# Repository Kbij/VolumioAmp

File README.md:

# VolumioAmp
A Raspberry Pi CM4 Volumio Amplifier combination

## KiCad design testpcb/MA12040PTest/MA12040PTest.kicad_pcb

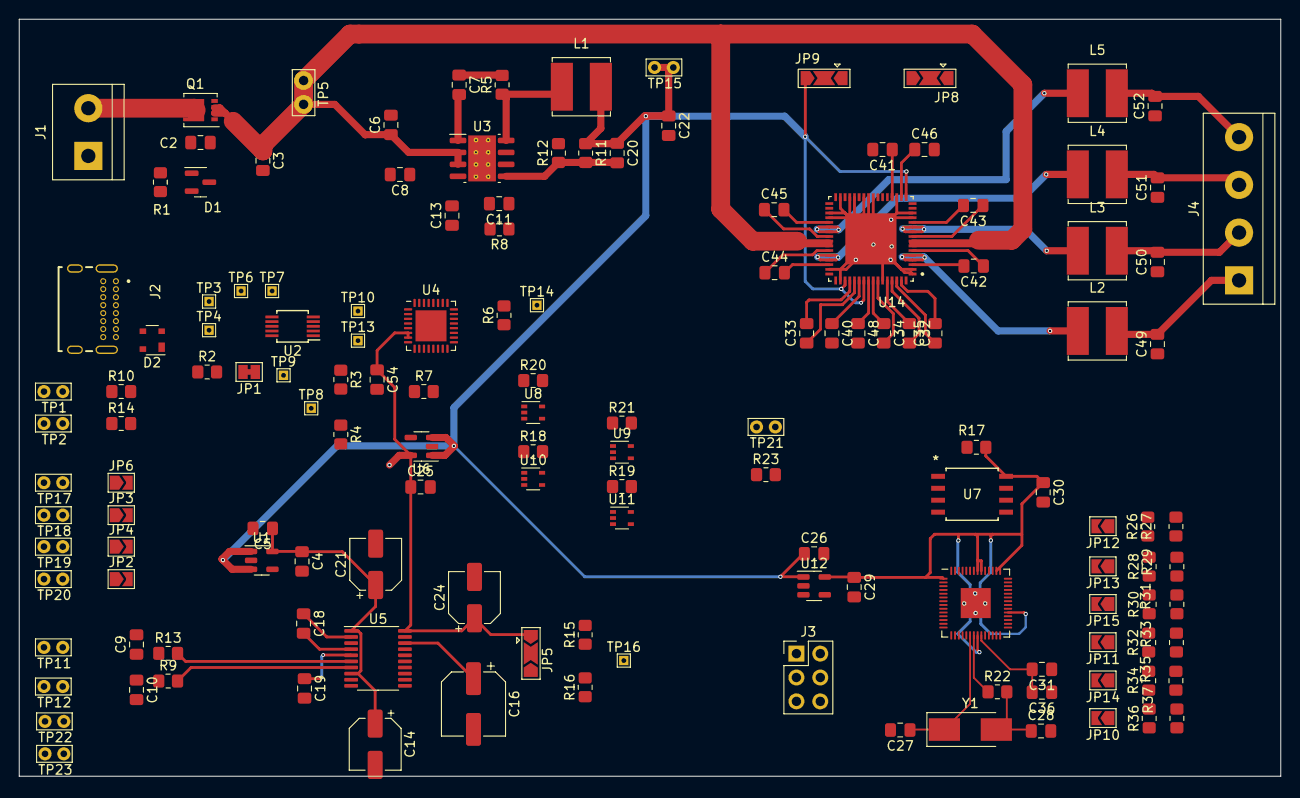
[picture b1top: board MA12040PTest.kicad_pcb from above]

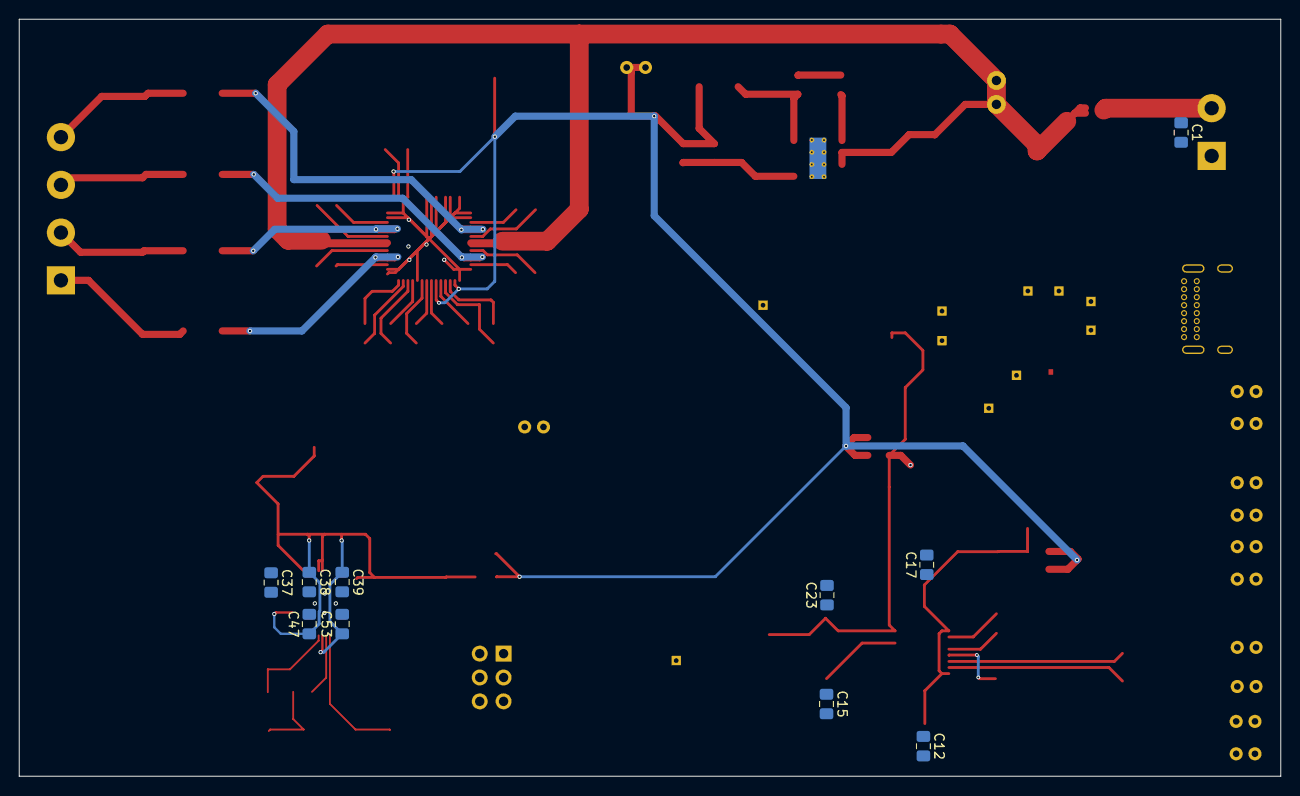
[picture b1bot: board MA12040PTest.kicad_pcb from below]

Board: 2 copper layers, 134.3 x 80.6 mm, 153 parts (10 on the bottom side), 100 nets.

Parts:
C1, C2, C7, C8, C12, C15, C17, C23, C30, C31, C35, C37, C38, C39, C47, C53: 100n; C_0805_2012Metric_Pad1.18x1.45mm_HandSolder
C3, C6: 10u 35v; C_0805_2012Metric_Pad1.18x1.45mm_HandSolder
C4: 10n; C_0805_2012Metric_Pad1.18x1.45mm_HandSolder
C5, C25, C26, C29, C32, C33, C34, C36, C40, C41, C46, C48, C49, C50, C51, C52, C54: 1u; C_0805_2012Metric_Pad1.18x1.45mm_HandSolder
C9, C10: 2n2; C_0805_2012Metric_Pad1.18x1.45mm_HandSolder
C11, C20: 220p; C_0805_2012Metric_Pad1.18x1.45mm_HandSolder
C13: 1.2nF; C_0805_2012Metric_Pad1.18x1.45mm_HandSolder
C14, C21, C24: 10u; CP_Elec_5x5.8
C16: 10u; CP_Elec_6.3x3.9
C18, C19: 2u2; C_0805_2012Metric_Pad1.18x1.45mm_HandSolder
C22, C42, C43, C44, C45: 10u; C_0805_2012Metric_Pad1.18x1.45mm_HandSolder
C27, C28: 22p; C_0805_2012Metric_Pad1.18x1.45mm_HandSolder
D1: MMBZ5242BLT3G; SOT-23
D2: SP0503BAHT; SOT-143
J1: 24v Input; TerminalBlock_bornier-2_P5.08mm
J2: USB4085-GF-A_REVB; GCT_USB4085-GF-A_REVB
J3: Conn_02x03_Top_Bottom; PinHeader_2x03_P2.54mm_Vertical
J4: Screw_Terminal_01x04; TerminalBlock_bornier-4_P5.08mm
JP1: USB-VBUS; SolderJumper-2_P1.3mm_Bridged_Pad1.0x1.5mm
JP2: MCLK; SolderJumper-2_P1.3mm_Open_TrianglePad1.0x1.5mm
JP3: LRCLK; SolderJumper-2_P1.3mm_Open_TrianglePad1.0x1.5mm
JP4: SCLK; SolderJumper-2_P1.3mm_Open_TrianglePad1.0x1.5mm
JP5: FMT; SolderJumper-3_P2.0mm_Open_TrianglePad1.0x1.5mm
JP6: D; SolderJumper-2_P1.3mm_Open_TrianglePad1.0x1.5mm
JP8: MUTE; SolderJumper-3_P2.0mm_Open_TrianglePad1.0x1.5mm
JP9: ENABLE; SolderJumper-3_P2.0mm_Open_TrianglePad1.0x1.5mm
JP10, JP11, JP12, JP13, JP14, JP15: SolderJumper-2_P1.3mm_Open_TrianglePad1.0x1.5mm
L1: SRN6045TA-3R3Y; L_Bourns_SRN6045TA
L2, L3, L4, L5: 0.5u; L_Bourns_SRN6045TA
Q1: DMP3013SFV-7; Diodes_PowerDI3333-8
R1, R11: 12K 1%; R_0805_2012Metric_Pad1.20x1.40mm_HandSolder
R2, R10, R14, R26, R27, R28, R29, R30, R31, R32, R33, R34, R35, R36, R37: 1k5; R_0805_2012Metric_Pad1.20x1.40mm_HandSolder
R3: 24k; R_0805_2012Metric_Pad1.20x1.40mm_HandSolder
R4: 47k; R_0805_2012Metric_Pad1.20x1.40mm_HandSolder
R5: 10R; R_0805_2012Metric_Pad1.20x1.40mm_HandSolder
R6, R7: 4k7; R_0805_2012Metric_Pad1.20x1.40mm_HandSolder
R8: 20K 1%; R_0805_2012Metric_Pad1.20x1.40mm_HandSolder
R9, R13, R15, R16: 470R; R_0805_2012Metric_Pad1.20x1.40mm_HandSolder
R12: 2.2K 1%; R_0805_2012Metric_Pad1.20x1.40mm_HandSolder
R17, R23: 10k; R_0805_2012Metric_Pad1.20x1.40mm_HandSolder
R18, R19, R20, R21: 33R; R_0805_2012Metric_Pad1.20x1.40mm_HandSolder
R22: 1k; R_0805_2012Metric_Pad1.20x1.40mm_HandSolder
TP1, TP17, TP18, TP19, TP20: SCL; TestPoint_Bridge_Pitch2.0mm_Drill0.7mm
TP2: SDA; TestPoint_Bridge_Pitch2.0mm_Drill0.7mm
TP3, TP4, TP8, TP9, TP10, TP13, TP14, TP16: TestPoint; TestPoint_THTPad_1.0x1.0mm_Drill0.5mm
TP5: TestPoint; TestPoint_Bridge_Pitch2.54mm_Drill1.0mm
TP6: USB_P; TestPoint_THTPad_1.0x1.0mm_Drill0.5mm
TP7: USB_N; TestPoint_THTPad_1.0x1.0mm_Drill0.5mm
TP11: L-Out; TestPoint_Bridge_Pitch2.0mm_Drill0.7mm
TP12: R-Out; TestPoint_Bridge_Pitch2.0mm_Drill0.7mm
TP15: TestPoint; TestPoint_Bridge_Pitch2.0mm_Drill0.7mm
TP21: Reset; TestPoint_Bridge_Pitch2.0mm_Drill0.7mm
TP22: RP_SCL; TestPoint_Bridge_Pitch2.0mm_Drill0.7mm
TP23: RP_SDA; TestPoint_Bridge_Pitch2.0mm_Drill0.7mm
U1: LT1761-3.3; TSOT-23-5
U2: FSUSB42MUX; MSOP-10_3x3mm_P0.5mm
U3: AP64501SP-13; SOIC-8-1EP_3.9x4.9mm_P1.27mm_EP2.95x4.9mm_Mask2.71x3.4mm_Th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
U4: CP2615-xx-xM; QFN-32-1EP_5x5mm_P0.5mm_EP3.3x3.3mm
U5: PCM5101A; TSSOP-20_4.4x6.5mm_P0.65mm
U6, U12: AP2112K-3.3; SOT-23-5
U7: S25FL064LABMFI010; SOIC8_208MIL_CYP
U8, U9, U10, U11: 74LVC1G07SE-7; SOT-353_SC-70-5
U13: RP2040; QFN-56-1EP_7x7mm_P0.4mm_EP3.2x3.2mm
U14: MA12040PXUMA1; QFN50P900X900X90-65N
Y1: 12Mhz; Crystal_SMD_Abracon_ABM3-2Pin_5.0x3.2mm_HandSoldering

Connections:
/+3.3v: C23.1, C24.1, C25.1, C54.1, JP5.1 (A), R3.1, R6.1, R7.1, R10.1, R14.1, R15.2, R26.1, R28.1, R30.1, R32.1, R34.1, R36.1, U2.1 (VCC), U4.6 (VDD), U4.7 (REGIN), U5.20 (DVDD), U6.5 (VOUT), U8.5 (VCC), U9.5 (VCC), U10.5 (VCC), U11.5 (VCC)
/+5v: C20.1, C22.1, C26.1, C40.2, JP8.3 (B), JP9.3 (B), L1.2, R11.1, TP15.1, U1.1 (VIN), U1.3 (~SHDN), U6.1 (VIN), U6.3 (EN), U12.1 (VIN), U12.3 (EN), U14.17 (AVDD), U14.51 (MSEL0), U14.55 (DVDD)
/+12v: C2.1, C3.1, C6.1, D1.3 (K), Q1.1 (S), Q1.2 (S), Q1.3 (S), TP5.1, U3.2 (VIN), U3.3 (EN), U14.7 (PVDD), U14.8 (PVDD), U14.41 (PVDD), U14.42 (PVDD)
/+Pico 3.3v: C29.1, C30.1, C37.1, C38.1, C39.1, C47.1, C53.1, R17.2, R23.2, U7.8 (VCC), U12.5 (VOUT), U13.1 (IOVDD), U13.10 (IOVDD), U13.22 (IOVDD), U13.33 (IOVDD), U13.42 (IOVDD), U13.43 (ADC_AVDD), U13.44 (VREG_IN), U13.48 (USB_VDD), U13.49 (IOVDD)
/BCK: JP4.1 (A), R18.1, R18.2, TP19.1, U5.13 (BCK), U10.2, U10.4, U14.21 (SCK)
/CFGMODE: JP13.1 (A), R6.2, R28.2, R29.1, TP14.1, U4.21 (~CFGMODE)
/D: JP6.1 (A), R20.1, R20.2, TP17.1, U5.14 (DIN), U8.2, U8.4, U14.23 (SD0)
/LRCK: JP3.1 (A), R21.1, R21.2, TP18.1, U5.15 (LRCK), U9.2, U9.4, U14.22 (WS)
/MCK: JP2.1 (A), R19.1, R19.2, TP20.1, U5.12 (SCK), U11.2, U11.4, U14.32 (CLK)
/PICO_SCL: JP11.1 (A), R10.2, R32.2, R33.1, TP1.1, U4.29 (I2C_SCL), U14.27 (SCL)
/PICO_SDA: JP15.1 (A), R14.2, R30.2, R31.1, TP2.1, U4.30 (I2C_SDA), U14.30 (SDA)
/RX: J3.4, U13.2 (GPIO0)
/SOUND_RESET: JP12.1 (A), R7.2, R26.2, R27.1, U4.9 (~RST)
/USBS_N: TP10.1, U2.4 (D_N), U4.5 (D-)
/USBS_P: TP13.1, U2.3 (D_P), U4.4 (D+)
/USB_DET: JP1.2 (B), JP10.1 (A), R2.2, R36.2, R37.1
/USB_SEL: JP1.1 (A), JP14.1 (A), R34.2, R35.1, TP9.1, U2.2 (SEL)
GND: C1.2, C3.2, C5.2, C6.2, C8.2, C9.2, C10.2, C11.2, C12.2, C13.2, C14.2, C15.2, C16.2, C17.2, C19.2, C21.2, C22.2, C23.2, C24.2, C25.2, C26.2, C27.2, C28.2, C29.2, C30.2, C31.1, C36.1, C37.2, C38.2, C39.2, C41.2, C46.2, C47.2, C48.2, C49.1, C50.1, C51.1, C52.1, C53.2, C54.2, D2.1 (A), J1.1, J2.A1 (GND), J2.A12 (GND), J2.B1 (GND), J2.B12 (GND), J2.S1 (SHELL), J2.S2 (SHELL), J2.S3 (SHELL), J2.S4 (SHELL), J3.1, JP5.3 (B), JP8.1 (A), JP9.1 (A), R1.2, R4.2, R12.2, R16.1, R27.2, R29.2, R31.2, R33.2, R35.2, R37.2, U1.2 (GND), U2.5 (GND), U2.10 (nOE), U3.7 (GND), U3.9 (EP), U4.3 (GND), U4.33 (GND), U5.3 (CPGND), U5.9 (AGND), U5.10 (DEMP), U5.11 (FLT), U5.19 (DGND), U6.2 (GND), U7.4 (VSS), U8.3 (GND), U9.3 (GND), U10.3 (GND), U11.3 (GND), U12.2 (GND), U13.57 (GND), U14.1 (PVSS), U14.2 (PVSS), U14.13 (PVSS), U14.14 (PVSS), U14.19 (AVSS), U14.24 (SD1), U14.25 (AVSS), U14.26 (DVSS), U14.28 (AD0), U14.29 (AD1), U14.31 (CLKM/S), U14.35 (PVSS), U14.36 (PVSS), U14.47 (PVSS), U14.48 (PVSS), U14.50 (MSEL1), U14.59 (DVSS), U14.65 (EXP)
unnamed: C7.1, R5.2
unnamed: C9.1, R13.1, TP11.1
unnamed: C10.1, R9.1, TP12.1
unnamed: C13.1, R8.2
unnamed: C28.1, R22.2, Y1.2
unnamed: C2.2, D1.1 (A), Q1.4 (G), R1.1
unnamed: D2.4 (K), J2.A4 (VBUS), J2.A9 (VBUS), J2.B4 (VBUS), J2.B9 (VBUS), R2.1
unnamed: C1.1, J1.2, Q1.5 (D)
unnamed: D2.2 (K), J2.A7 (DN1), J2.B7 (DN2), TP4.1, U2.9 (HSD1_P)
unnamed: D2.3 (K), J2.A6 (DP1), J2.B6 (DP2), TP3.1, U2.8 (HSD1_M)
unnamed: J3.2, U13.24 (SWCLK)
unnamed: J3.6, U13.25 (SWD)
unnamed: C49.2, J4.1, L2.2
unnamed: C50.2, J4.2, L3.2
unnamed: C51.2, J4.3, L4.2
unnamed: C52.2, J4.4, L5.2
unnamed: JP2.2 (B), U4.26 (I2S_MCLK)
unnamed: JP3.2 (B), U4.28 (I2S_LRCLK)
unnamed: JP4.2 (B), U4.2 (I2S_SCLK)
unnamed: JP5.2 (C), U5.16 (FMT)
unnamed: JP6.2 (B), U4.32 (I2S_SDOUT)
unnamed: JP8.2 (C), U14.34 (~MUTE)
unnamed: JP9.2 (C), U14.33 (~ENABLE)
unnamed: JP10.2 (B), U13.29 (GPIO18)
unnamed: JP11.2 (B), U13.31 (GPIO20)
unnamed: JP12.2 (B), U13.37 (GPIO25)
unnamed: JP13.2 (B), U13.36 (GPIO24)
unnamed: JP14.2 (B), U13.30 (GPIO19)
unnamed: JP15.2 (B), U13.32 (GPIO21)
unnamed: L2.1, U14.4 (OUT0A), U14.5 (OUT0A)
unnamed: L3.1, U14.10 (OUT0B), U14.11 (OUT0B)
unnamed: L4.1, U14.44 (OUT1A), U14.45 (OUT1A)
unnamed: L5.1, U14.38 (OUT1B), U14.39 (OUT1B)
unnamed: C4.2, U1.4 (BYP)
unnamed: C4.1, C5.1, C12.1, C14.1, C17.1, C21.1, U1.5 (VOUT), U5.1 (CPVDD), U5.8 (AVDD)
unnamed: TP7.1, U2.6 (HSD0_M)
unnamed: TP6.1, U2.7 (HSD0_P)
unnamed: C7.2, U3.1 (BST)
unnamed: C11.1, R8.1, U3.6 (COMP)
unnamed: C20.2, R11.2, R12.1, U3.5 (FB)
unnamed: C8.1, U3.4 (SS)
unnamed: L1.1, R5.1, U3.8 (SW)
unnamed: R3.2, R4.1, TP8.1, U4.8 (VBUS)
unnamed: C18.2, U5.4 (CAPM)
unnamed: C18.1, U5.2 (CAPP)
unnamed: C15.1, C16.1, U5.18 (LDOO)
unnamed: R13.2, U5.6 (OUTL)
unnamed: R9.2, U5.7 (OUTR)
unnamed: C19.1, U5.5 (VNEG)
unnamed: R15.1, R16.2, TP16.1, U5.17 (XSMT)
unnamed: TP22.1, U13.34 (GPIO22)
unnamed: TP23.1, U13.35 (GPIO23)
unnamed: U7.6 (SCK), U13.52 (QSPI_SCLK)
unnamed: U7.5 (SI/IO0), U13.53 (QSPI_SD0)
unnamed: U7.2 (SO/IO1), U13.55 (QSPI_SD1)
unnamed: U7.3 (WP#/IO2), U13.54 (QSPI_SD2)
unnamed: U7.7 (IO3/RESET#), U13.51 (QSPI_SD3)
unnamed: R17.1, U7.1 (CS#), U13.56 (QSPI_SS)
unnamed: R23.1, TP21.1, U13.26 (RUN)
unnamed: C31.2, C36.2, U13.23 (DVDD), U13.45 (VREG_VOUT), U13.50 (DVDD)
unnamed: C27.1, U13.20 (XIN), Y1.1
unnamed: R22.1, U13.21 (XOUT)
unnamed: C48.1, U14.56 (CDC)
unnamed: C42.2, U14.3 (CF0AN)
unnamed: C42.1, U14.6 (CF0AP)
unnamed: C43.2, U14.12 (CF0BN)
unnamed: C43.1, U14.9 (CF0BP)
unnamed: C44.2, U14.46 (CF1AN)
unnamed: C44.1, U14.43 (CF1AP)
unnamed: C45.2, U14.37 (CF1BN)
unnamed: C45.1, U14.40 (CF1BP)
unnamed: C34.2, U14.58 (CFDCN)
unnamed: C34.1, U14.57 (CFDCP)
unnamed: C35.2, U14.63 (CFGDN)
unnamed: C35.1, U14.62 (CFGDP)
unnamed: C32.2, U14.61 (CGD0N)
unnamed: C32.1, U14.60 (CGD0P)
unnamed: C33.2, U14.52 (CGD1N)
unnamed: C33.1, U14.53 (CGD1P)
unnamed: C46.1, U14.18 (CMSE)
unnamed: C41.1, U14.20 (CREF)
unnamed: C40.1, U14.54 (VGDC)

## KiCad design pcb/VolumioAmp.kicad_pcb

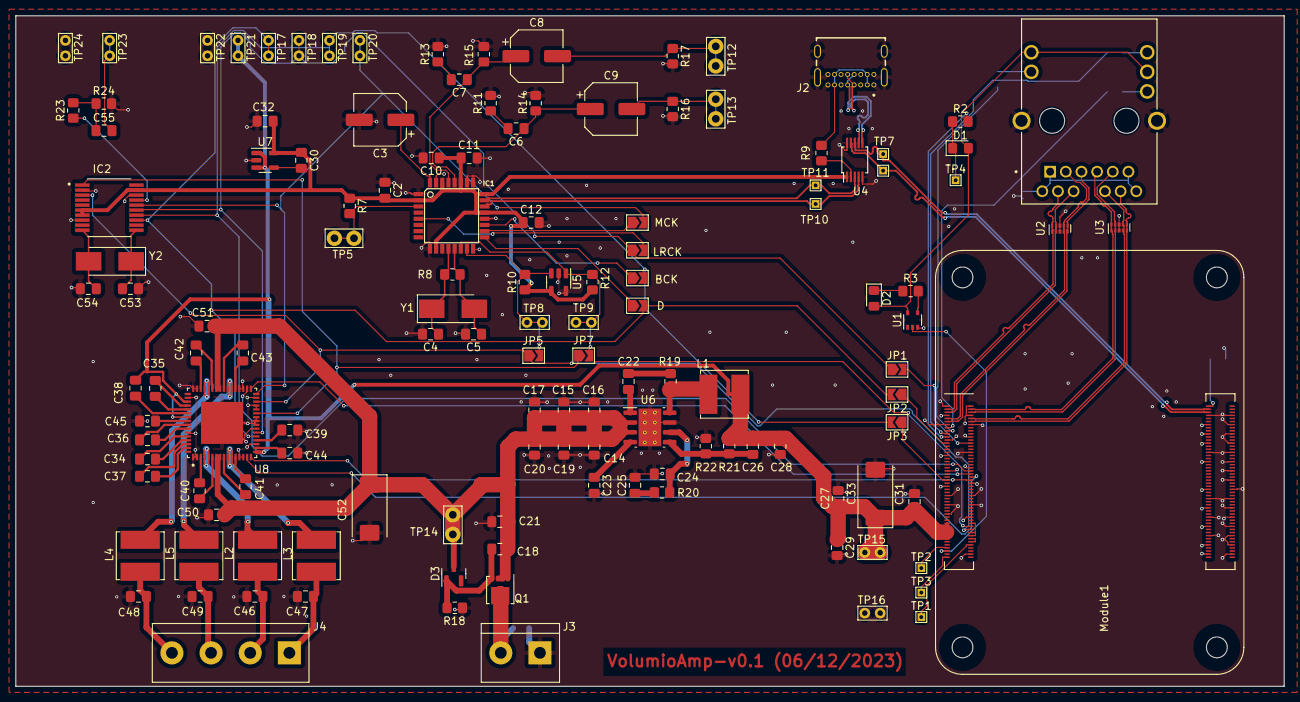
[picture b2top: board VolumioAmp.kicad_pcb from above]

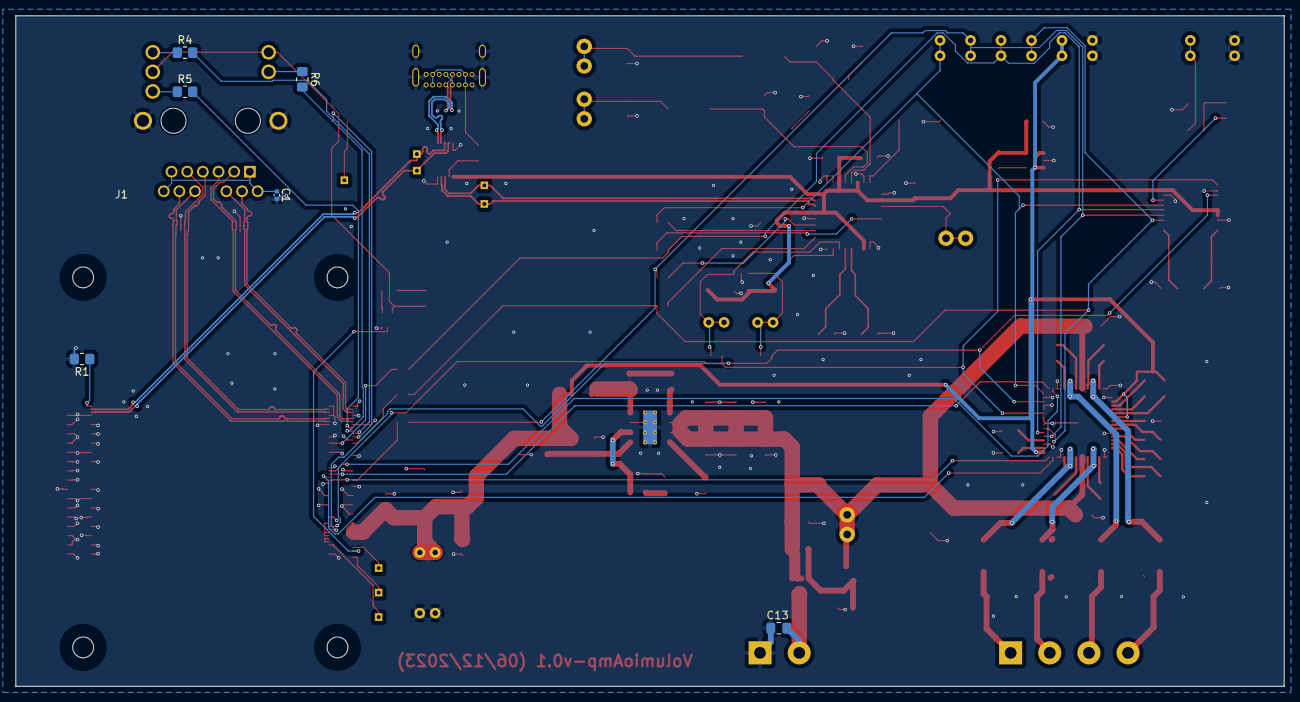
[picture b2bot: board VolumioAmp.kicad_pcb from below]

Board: 4 copper layers, 164.6 x 87.0 mm, 138 parts (6 on the bottom side), 111 nets.

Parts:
C1: 100n; C_0402_1005Metric
C2, C10, C11, C32, C34, C35, C36, C38, C39, C44, C45, C46, C47, C48, C49, C50, C51: 1u; C_0805_2012Metric_Pad1.18x1.45mm_HandSolder
C3: 10u; CP_Elec_6.3x3.9
C4, C5, C6, C7, C53, C54: 22n; C_0805_2012Metric_Pad1.18x1.45mm_HandSolder
C8, C9: 100u; CP_Elec_6.3x3.9
C12, C18, C22, C23, C37: 100n; C_0805_2012Metric_Pad1.18x1.45mm_HandSolder
C13: 100n 100v; C_0805_2012Metric_Pad1.18x1.45mm_HandSolder
C14, C15, C16, C17, C19, C20, C21: 10u 35v; C_0805_2012Metric_Pad1.18x1.45mm_HandSolder
C24, C26: nf; C_0805_2012Metric_Pad1.18x1.45mm_HandSolder
C25: 1.2nF; C_0805_2012Metric_Pad1.18x1.45mm_HandSolder
C27, C28, C29, C31, C40, C41, C42, C43: 10u; C_0805_2012Metric_Pad1.18x1.45mm_HandSolder
C30: 10n; C_0805_2012Metric_Pad1.18x1.45mm_HandSolder
C33: 100uF; CP_EIA-7343-31_Kemet-D
C52: 470u; CP_EIA-7343-31_Kemet-D
C55: C; C_0805_2012Metric_Pad1.18x1.45mm_HandSolder
D1: LED Green; LED_0805_2012Metric_Pad1.15x1.40mm_HandSolder
D2: LED Red; LED_0805_2012Metric_Pad1.15x1.40mm_HandSolder
D3: MMBZ5242BLT3G; SOT-23
IC1: PCM2706; TQFP32-08
IC2: WM8804GEDS_V; SOP65P780X200-20N
J1: L829-1J1T-43; BEL_L829-1J1T-43
J2: USB4085-GF-A_REVB; GCT_USB4085-GF-A_REVB
J3: 24v Input; TerminalBlock_bornier-2_P5.08mm
J4: Screw_Terminal_01x04; TerminalBlock_bornier-4_P5.08mm
JP1, JP4: LRCK; SolderJumper-2_P1.3mm_Open_TrianglePad1.0x1.5mm
JP2, JP9: D; SolderJumper-2_P1.3mm_Open_TrianglePad1.0x1.5mm
JP3, JP6: BCK; SolderJumper-2_P1.3mm_Open_TrianglePad1.0x1.5mm
JP5: SDA; SolderJumper-2_P1.3mm_Open_TrianglePad1.0x1.5mm
JP7: SCL; SolderJumper-2_P1.3mm_Open_TrianglePad1.0x1.5mm
JP8: MCK; SolderJumper-2_P1.3mm_Open_TrianglePad1.0x1.5mm
L1: SRN6045TA-3R3Y; L_Bourns_SRN6045TA
L2, L3, L4, L5: L; L_Bourns_SRN6045TA
Module1: ComputeModule4; Raspberry-Pi-4-Compute-Module
Q1: DMP3013SFV-7; Diodes_PowerDI3333-8
R1, R9, R22: 2.2K 1%; R_0805_2012Metric_Pad1.20x1.40mm_HandSolder
R2, R3, R7: 1k; R_0805_2012Metric_Pad1.20x1.40mm_HandSolder
R4, R5, R6: 470R; R_0805_2012Metric_Pad1.20x1.40mm_HandSolder
R8: 1M; R_0805_2012Metric_Pad1.20x1.40mm_HandSolder
R10, R12: 1k5; R_0805_2012Metric_Pad1.20x1.40mm_HandSolder
R11, R13: 13R; R_0805_2012Metric_Pad1.20x1.40mm_HandSolder
R14, R15, R16, R17: 3k3; R_0805_2012Metric_Pad1.20x1.40mm_HandSolder
R18, R21: 12K 1%; R_0805_2012Metric_Pad1.20x1.40mm_HandSolder
R19: 10R; R_0805_2012Metric_Pad1.20x1.40mm_HandSolder
R20: 20K 1%; R_0805_2012Metric_Pad1.20x1.40mm_HandSolder
R23, R24: R; R_0805_2012Metric_Pad1.20x1.40mm_HandSolder
TP1, TP2, TP3, TP4, TP6, TP7, TP10, TP11: TestPoint; TestPoint_THTPad_1.0x1.0mm_Drill0.5mm
TP5: Host; TestPoint_Bridge_Pitch2.54mm_Drill1.0mm
TP8, TP9, TP15, TP16, TP23, TP24: TestPoint; TestPoint_Bridge_Pitch2.0mm_Drill0.7mm
TP12: Out R; TestPoint_Bridge_Pitch2.54mm_Drill1.0mm
TP13: Out L; TestPoint_Bridge_Pitch2.54mm_Drill1.0mm
TP14: TestPoint; TestPoint_Bridge_Pitch2.54mm_Drill1.0mm
TP17, TP21, TP22: D; TestPoint_Bridge_Pitch2.0mm_Drill0.7mm
TP18: LRCK; TestPoint_Bridge_Pitch2.0mm_Drill0.7mm
TP19: BCK; TestPoint_Bridge_Pitch2.0mm_Drill0.7mm
TP20: MCK; TestPoint_Bridge_Pitch2.0mm_Drill0.7mm
U1: 74LVC1G07SE-7; SOT-353_SC-70-5
U2, U3: TPD4EUSB30; USON-10_2.5x1.0mm_P0.5mm
U4: FSUSB42MUX; MSOP-10_3x3mm_P0.5mm
U5: 24AA02-OT; SOT-23-5
U6: AP64501SP-13; SOIC-8-1EP_3.9x4.9mm_P1.27mm_EP2.95x4.9mm_Mask2.71x3.4mm_Th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
U7: LT1761-3.3; TSOT-23-5
U8: MA12040PXUMA1; QFN50P900X900X90-65N
Y1, Y2: 12Mhz; Crystal_SMD_Abracon_ABM3-2Pin_5.0x3.2mm_HandSoldering

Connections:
/Amplifier/+24v: C14.1, C15.1, C16.1, C17.1, C18.1, C19.1, C20.1, C21.1, C50.2, C51.2, C52.1, D3.3 (K), Q1.1 (S), Q1.2 (S), Q1.3 (S), TP14.1, U6.2 (VIN), U6.3 (EN), U8.7 (PVDD), U8.8 (PVDD), U8.41 (PVDD), U8.42 (PVDD)
/Amplifier/AC.~CLIP: Module1.48 (GPIO27), U8.15 (~CLIP)
/Amplifier/AC.~ENABLE: Module1.46 (GPIO22), U8.33 (~ENABLE)
/Amplifier/AC.~ERROR: Module1.50 (GPIO17), U8.16 (~ERROR)
/Amplifier/AC.~MUTE: Module1.44 (GPIO10), U8.34 (~MUTE)
/Amplifier/I2S.BCK: IC2.14 (BCLK), JP3.2 (B), JP6.2 (B), TP19.1, U8.21 (SCK)
/Amplifier/I2S.D: IC2.13 (DIN), JP2.2 (B), JP9.2 (B), TP17.1, U8.23 (SD0)
/Amplifier/I2S.LRCK: IC2.15 (LRCLK), JP1.1 (A), JP4.1 (A), TP18.1, U8.22 (WS)
/Amplifier/I2S.MCK: IC2.16 (MCLK), JP8.2 (B), TP20.1, U8.32 (CLK)
/Amplifier/SCL: IC2.1 (SCLK), JP7.1 (A), Module1.80 (SCL0), U8.27 (SCL)
/Amplifier/SDA: IC2.3 (SDIN/HWMODE), JP5.1 (A), Module1.82 (SDA0), U8.30 (SDA)
/CM4_Ethernet/+3.3v: D1.2 (A), D2.2 (A), J1.14, J1.16, U1.5 (VCC)
/CM4_Ethernet/+5v: C26.1, C27.1, C28.1, C29.1, C31.1, C33.1, C38.2, L1.2, Module1.77 (+5v_(Input)), Module1.79 (+5v_(Input)), Module1.81 (+5v_(Input)), Module1.83 (+5v_(Input)), Module1.85 (+5v_(Input)), Module1.87 (+5v_(Input)), R21.1, TP15.1, TP21.1, U7.1 (VIN), U7.3 (~SHDN), U8.17 (AVDD), U8.51 (MSEL0), U8.55 (DVDD)
/CM4_Ethernet/ETH_LEDG: Module1.17 (Ethernet_nLED2(3.3v)), R6.2
/CM4_Ethernet/ETH_LEDY: Module1.15 (Ethernet_nLED3(3.3v)), R5.2
/CM4_Ethernet/GPIO18: JP3.1 (A), Module1.49 (GPIO18)
/CM4_Ethernet/GPIO19: JP1.2 (B), Module1.26 (GPIO19)
/CM4_Ethernet/GPIO21: JP2.1 (A), Module1.25 (GPIO21)
/CM4_Ethernet/TRD0_N: J1.10 (TRD1-), Module1.10 (Ethernet_Pair0_N), U3.4 (D2+), U3.7
/CM4_Ethernet/TRD0_P: J1.11 (TRD1+), Module1.12 (Ethernet_Pair0_P), U3.5 (D2-), U3.6
/CM4_Ethernet/TRD1_N: J1.5 (TRD2-), Module1.6 (Ethernet_Pair1_N), U3.2 (D1-), U3.9
/CM4_Ethernet/TRD1_P: J1.4 (TRD2+), Module1.4 (Ethernet_Pair1_P), U3.1 (D1+), U3.10
/CM4_Ethernet/TRD2_N: J1.2 (TRD3-), Module1.9 (Ethernet_Pair2_N), U2.4 (D2+), U2.7
/CM4_Ethernet/TRD2_P: J1.3 (TRD3+), Module1.11 (Ethernet_Pair2_P), U2.5 (D2-), U2.6
/CM4_Ethernet/TRD3_N: J1.9 (TRD4-), Module1.5 (Ethernet_Pair3_N), U2.2 (D1-), U2.9
/CM4_Ethernet/TRD3_P: J1.8 (TRD4+), Module1.3 (Ethernet_Pair3_P), U2.1 (D1+), U2.10
/CM4_Ethernet/nPWR_LED: Module1.95 (nPI_LED_PWR), U1.2
/CM4_HighSpeed/USB2_N: Module1.103 (USB2_N), TP7.1, U4.8 (HSD1_M)
/CM4_HighSpeed/USB2_P: Module1.105 (USB2_P), TP6.1, U4.9 (HSD1_P)
/I2STest/+3.3v: C2.2, C10.1, C11.1, C12.1, C30.1, C32.1, IC1.2 (VCCP), IC1.10 (TEST), IC1.21 (VDD), IC1.24 (VBUS), IC1.27 (VCCL), IC1.30 (VCCR), IC2.6 (RESETB), IC2.7 (PVDD), IC2.19 (DVDD), R7.1, R10.1, R12.1, U4.1 (VCC), U5.4 (V_{CC}), U7.5 (VOUT)
/USB_Sound/USBD_N: J2.A7 (DN1), J2.B7 (DN2), U4.6 (HSD0_M)
/USB_Sound/USBD_P: J2.A6 (DP1), J2.B6 (DP2), U4.7 (HSD0_P)
/USB_Sound/USBS_N: IC1.22 (D-), TP10.1, U4.4 (D_N)
/USB_Sound/USBS_P: IC1.23 (D+), TP11.1, U4.3 (D_P)
GND: C1.2, C2.1, C3.2, C4.2, C5.2, C10.2, C11.2, C12.2, C13.2, C14.2, C15.2, C16.2, C17.2, C19.2, C20.2, C21.2, C23.2, C24.2, C25.2, C27.2, C28.2, C29.2, C31.2, C32.2, C33.2, C39.2, C44.2, C45.2, C46.1, C47.1, C48.1, C49.1, C50.1, C51.1, C52.2, C53.2, C54.2, IC1.1 (PGND), IC1.9 (FSEL), IC1.16 (PSEL), IC1.20 (DGND), IC1.25 (ZGND), IC1.26 (AGNDL), IC1.31 (AGNDR), IC2.2 (GPO0/SWIFMODE), IC2.8 (PGND), IC2.18 (DGND), J1.S1 (SHIELD), J1.S2 (SHIELD), J2.A1 (GND), J2.A12 (GND), J2.B1 (GND), J2.B12 (GND), J2.S1 (SHELL), J2.S2 (SHELL), J2.S3 (SHELL), J2.S4 (SHELL), J3.1, Module1.1 (GND), Module1.2 (GND), Module1.7 (GND), Module1.8 (GND), Module1.13 (GND), Module1.14 (GND), Module1.22 (GND), Module1.23 (GND), Module1.32 (GND), Module1.33 (GND), Module1.42 (GND), Module1.43 (GND), Module1.52 (GND), Module1.53 (GND), Module1.59 (GND), Module1.60 (GND), Module1.65 (GND), Module1.66 (GND), Module1.71 (GND), Module1.74 (GND), Module1.98 (GND), Module1.107 (GND), Module1.108 (GND), Module1.113 (GND), Module1.114 (GND), Module1.119 (GND), Module1.120 (GND), Module1.125 (GND), Module1.126 (GND), Module1.131 (GND), Module1.132 (GND), Module1.137 (GND), Module1.138 (GND), Module1.144 (GND), Module1.150 (GND), Module1.155 (GND), Module1.156 (GND), Module1.161 (GND), Module1.162 (GND), Module1.167 (GND), Module1.168 (GND), Module1.173 (GND), Module1.174 (GND), Module1.179 (GND), Module1.180 (GND), Module1.185 (GND), Module1.186 (GND), Module1.191 (GND), Module1.192 (GND), Module1.197 (GND), Module1.198 (GND), R1.2, R11.2, R13.2, R14.2, R15.2, R16.2, R17.2, R18.2, R22.2, R24.2, TP16.1, TP22.1, TP24.1, U1.3 (GND), U2.3 (GND), U2.8 (GND), U3.3 (GND), U3.8 (GND), U4.5 (GND), U4.10 (nOE), U5.2 (V_{SS}), U5.5 (WP), U6.7 (GND), U6.9 (EP), U7.2 (GND), U8.1 (PVSS), U8.2 (PVSS), U8.13 (PVSS), U8.14 (PVSS), U8.19 (AVSS), U8.24 (SD1), U8.25 (AVSS), U8.26 (DVSS), U8.28 (AD0), U8.29 (AD1), U8.31 (CLKM/S), U8.35 (PVSS), U8.36 (PVSS), U8.47 (PVSS), U8.48 (PVSS), U8.50 (MSEL1), U8.59 (DVSS), U8.65 (EXP)
unnamed: C6.2, R11.1
unnamed: C7.2, R13.1
unnamed: C8.2, R17.1, TP12.1
unnamed: C9.2, R16.1, TP13.1
unnamed: C22.1, R19.2
unnamed: C25.1, R20.2
unnamed: C55.1, R23.2, R24.1
unnamed: C55.2, TP23.1
unnamed: D1.1 (K), R2.1, TP4.1
unnamed: D2.1 (K), R3.1
unnamed: C18.2, D3.1 (A), Q1.4 (G), R18.1
unnamed: IC1.14 (CK), JP7.2 (B), R12.2, TP9.1, U5.1 (SCL)
unnamed: IC1.17 (DOUT), JP9.1 (A)
unnamed: IC1.15 (DT), JP5.2 (B), R10.2, TP8.1, U5.3 (SDA)
unnamed: IC1.5 (FUNC0), JP4.2 (B)
unnamed: IC1.19 (FUNC1), JP6.1 (A)
unnamed: IC1.18 (FUNC2), JP8.1 (A)
unnamed: IC1.3 (HOST), R7.2, TP5.1
unnamed: C3.1, IC1.32 (VCOM)
unnamed: C6.1, C9.1, IC1.28 (VOUTL), R14.1
unnamed: C7.1, C8.1, IC1.29 (VOUTR), R15.1
unnamed: C4.1, IC1.12 (XTI), R8.1, Y1.1
unnamed: C5.1, IC1.13 (XTO), R8.2, Y1.2
unnamed: IC2.17 (TX0), R23.1
unnamed: C53.1, IC2.11 (XIN), Y2.1
unnamed: C54.1, IC2.10 (XOP), Y2.2
unnamed: J1.13, R6.1
unnamed: J1.15, R5.1
unnamed: J1.17, R4.1
unnamed: C1.1, J1.1 (TRCT3), J1.6 (TRCT2), J1.7 (TRCT4), J1.12 (TRCT1)
unnamed: J2.A4 (VBUS), J2.A9 (VBUS), J2.B4 (VBUS), J2.B9 (VBUS), R9.1
unnamed: C13.1, J3.2, Q1.5 (D)
unnamed: C47.2, J4.1, L3.2
unnamed: C46.2, J4.2, L2.2
unnamed: C49.2, J4.3, L5.2
unnamed: C48.2, J4.4, L4.2
unnamed: L2.1, U8.4 (OUT0A), U8.5 (OUT0A)
unnamed: L3.1, U8.10 (OUT0B), U8.11 (OUT0B)
unnamed: L4.1, U8.44 (OUT1A), U8.45 (OUT1A)
unnamed: L5.1, U8.38 (OUT1B), U8.39 (OUT1B)
unnamed: Module1.88 (+1.8v_(Output)), Module1.90 (+1.8v_(Output))
unnamed: Module1.19 (Ethernet_nLED1(3.3v)), R4.2
unnamed: Module1.78 (GPIO_VREF(1.8v/3.3v_Input)), Module1.84 (+3.3v_(Output)), Module1.86 (+3.3v_(Output))
unnamed: Module1.99 (Global_EN), TP3.1
unnamed: Module1.21 (PI_nLED_Activity), R2.2
unnamed: Module1.92 (RUN_PG), TP1.1
unnamed: Module1.93 (nRPIBOOT), TP2.1
unnamed: Module1.101 (USB_OTG_ID), R1.1
unnamed: R3.2, U1.4
unnamed: R9.2, U4.2 (SEL)
unnamed: C22.2, U6.1 (BST)
unnamed: C24.1, R20.1, U6.6 (COMP)
unnamed: C26.2, R21.2, R22.1, U6.5 (FB)
unnamed: C23.1, U6.4 (SS)
unnamed: L1.1, R19.1, U6.8 (SW)
unnamed: C30.2, U7.4 (BYP)
unnamed: C45.1, U8.56 (CDC)
unnamed: C40.2, U8.3 (CF0AN)
unnamed: C40.1, U8.6 (CF0AP)
unnamed: C41.2, U8.12 (CF0BN)
unnamed: C41.1, U8.9 (CF0BP)
unnamed: C42.2, U8.46 (CF1AN)
unnamed: C42.1, U8.43 (CF1AP)
unnamed: C43.2, U8.37 (CF1BN)
unnamed: C43.1, U8.40 (CF1BP)
unnamed: C36.2, U8.58 (CFDCN)
unnamed: C36.1, U8.57 (CFDCP)
unnamed: C37.2, U8.63 (CFGDN)
unnamed: C37.1, U8.62 (CFGDP)
unnamed: C34.2, U8.61 (CGD0N)
unnamed: C34.1, U8.60 (CGD0P)
unnamed: C35.2, U8.52 (CGD1N)
unnamed: C35.1, U8.53 (CGD1P)
unnamed: C44.1, U8.18 (CMSE)
unnamed: C39.1, U8.20 (CREF)
unnamed: C38.1, U8.54 (VGDC)

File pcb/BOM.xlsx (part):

Item | Qty | Reference(s) | Value | LibPart | Footprint | Datasheet | Availability | Check_prices | Description | Farnell | Field4 | Field5 | Field6 | Field7 | Field8 | MANUFACTURER | MAXIMUM_PACKAGE_HEIGHT | MF | MP | PARTREV | Package | Part Description | Price | Purchase-URL | SNAPEDA_PN | STANDARD | SnapEDA_Link
1 | 1 | C1 | 100n | Device:C | Capacitor_SMD:C_01005_0402Metric | https://search.murata.co.jp/Ceramy/image/img/A01X/G101/ENG/G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 |  |  |  | 2409031 | Farnell | 2409031 | RM EMK105 B7104KV-F | TAIYO YUDEN EUROPE GMBH | 110091611 |  |  |  |  |  |  | 0.1uF 10% 16V Ceramic Capacitor X7R 0402 (1005 Metric)
2 | 18 | C2, C10, C11, C32, C34, C35, C36, C38, C39, C44, C45, C46, C47, C48, C49, C50, 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 | 1u | Device:C | Capacitor_SMD:C_0805_2012Metric_Pad1.18x1.45mm_HandSolder | ~ |  |  |  | 3013482
3 | 1 | C3 | 10u | Device:C_Polarized | Capacitor_SMD:CP_Elec_6.3x3.9 | ~ |  |  |  | 1834254
4 | 4 | C4, C5, C53, C54 | 22p | Device:C | Capacitor_SMD:C_0805_2012Metric_Pad1.18x1.45mm_HandSolder | ~ |  |  |  | 2896721
5 | 2 | C6, C7 | 22n | Device:C | Capacitor_SMD:C_0805_2012Metric_Pad1.18x1.45mm_HandSolder | ~ |  |  |  | 1828943
6 | 2 | C8, C9 | 100u | Device:C_Polarized | Capacitor_SMD:CP_Elec_6.3x3.9 | ~ |  |  |  | 1187011
7 | 6 | C12, C13, C18, C22, C23, C37 | 100n | Device:C | Capacitor_SMD:C_0805_2012Metric_Pad1.18x1.45mm_HandSolder | ~ |  |  |  | 1414664 | Farnell | 2611907 | GRM155R62A104KE14D | Murata | 110091611 |  |  |  |  |  |  | 0.1uF 10% 100V Ceramic Capacitor X5R 0402 (1005 Metric)
8 | 7 | C14, C15, C16, C17, C19, C20, C21 | 10u 35v | Device:C | Capacitor_SMD:C_0805_2012Metric_Pad1.18x1.45mm_HandSolder | https://www.murata.com/en-global/products/productdetail.aspx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 |  |  |  | 2611943 | Digikey | 490-10505-1-ND | GRM21BC8YA106KE11L | Murata |  |  |  |  |  |  |  | 10uF 10% or 20% 35V Ceramic Capacitor X6S 0805 (2012 Metric)
9 | 2 | C24, C26 | 220p | Device:C | Capacitor_SMD:C_0805_2012Metric_Pad1.18x1.45mm_HandSolder | ~ |  |  |  | 2896723 | Farnell | 2666374 | GRM1555C1H221JA01D | Murata |  |  |  |  |  |  |  | 220 pF, 50 V, 0402 [1005 Metric], Â± 5%, C0G / NP0/CH, GCM Series
10 | 1 | C25 | 1.2nF | Device:C | Capacitor_SMD:C_0805_2012Metric_Pad1.18x1.45mm_HandSolder | http://www.farnell.com/datasheets/2734135.pdf?_ga=2.25934765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 |  |  |  | 1759229 | Digikey | 490-16429-1-ND | GCM155R71H122KA37D | Murata |  |  |  |  |  |  |  | 1200pF 10% 10V Ceramic Capacitor X5R 0402 (1005 Metric)
11 | 8 | C27, C28, C29, C31, C40, C41, C42, C43 | 10u | Device:C | Capacitor_SMD:C_0805_2012Metric_Pad1.18x1.45mm_HandSolder | https://search.murata.co.jp/Ceramy/image/img/A01X/G101/ENG/G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 |  |  |  | 2611943 | Digikey | 490-14381-1-ND | GRM21BR71A106KA73L | Murata | 111893011 |  |  |  |  |  |  | 10uF 10% 10V Ceramic Capacitor X7R 0805 (2012 Metric)
12 | 1 | C30 | 10n | Device:C | Capacitor_SMD:C_0805_2012Metric_Pad1.18x1.45mm_HandSolder | ~ |  |  |  | 9406352
13 | 1 | C33 | 100uF | Device:CP | Capacitor_Tantalum_SMD:CP_EIA-7343-31_Kemet-D | ~ |  |  |  | 4144905 | Mouser | 667-EEF-CX0J101R |  |  |  |  |  |  |  |  |  | Capacitor, SP-Cap, 100u, 6.3V, 15mR ESR
14 | 1 | C52 | 470u | Device:CP | Capacitor_Tantalum_SMD:CP_EIA-7343-31_Kemet-D | ~ |  |  |  | 4146798 | Mouser | 667-EEF-CX0J101R |  |  |  |  |  |  |  |  |  | Capacitor, SP-Cap, 100u, 6.3V, 15mR ESR
15 | 1 | D1 | LED Green | Device:LED | LED_SMD:LED_0805_2012Metric_Pad1.15x1.40mm_HandSolder | ~ |  |  |  | 2991544 | Digikey | LTST-S270KGKT | SML-A12M8TT86N | Rohm | 650263301 |  |  |  |  |  |  | Green 572nm LED Indication - Discrete 2.2V 2-SMD, No Lead
16 | 1 | D2 | LED Red | :LED_1 | LED_SMD:LED_0805_2012Metric_Pad1.15x1.40mm_HandSolder | ~ |  |  |  | 2991544 | Digikey | LTST-S270KRKT | SML-A12U8TT86Q | Rohm | 650295101 |  |  |  |  |  |  | Red 620nm LED Indication - Discrete 2.2V 2-SMD, No Lead
17 | 1 | D3 | MMBZ5242BLT3G | Diode:BZX84Cxx | Package_TO_SOT_SMD:SOT-23 | https://diotec.com/tl_files/diotec/files/pdf/datasheets/bzx8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 |  |  |  | 3607004 | Digikey | MMBZ5242BLT3GOSCT-ND | MMBZ5242BLT3G | Onsemi |  |  |  |  |  |  |  | Zener Diode 12V 225mW 5% Surface Mount SOT-23-3 (TO-236)
18 | 1 | IC1 | PCM2706 | PCM2706:PCM2706 | Footprints:TQFP32-08 |  | Not in stock | https://www.snapeda.com/parts/PCM2706/Burr+Brown/view-part/?ref=eda | Audio Audio Signal Processor 2 Channel 32-TQFP (7x7) | 3118707 |  |  |  |  |  |  |  | Burr Brown | PCM2706 |  | TQFP-32 Texas Instruments |  | None |  |  |  | https://www.snapeda.com/parts/PCM2706/Burr+Brown/view-part/?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
19 | 1 | IC2 | WM8804GEDS_V | WM8804GEDS_V:WM8804GEDS_V | Footprints:SOP65P780X200-20N |  | In Stock | https://www.snapeda.com/parts/WM8804GEDS/V/Cirrus+Logic+Inc.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 | Audio Audio Transceiver 1 Channel 20-SSOP |  |  |  |  |  |  |  |  | Cirrus Logic | WM8804GEDS/V |  | SSOP-20 Wolfson |  | None | https://www.snapeda.com/api/url_track_click_mouser/?unipart_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 |  |  | https://www.snapeda.com/parts/WM8804GEDS/V/Cirrus+Logic+Inc.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
20 | 1 | J1 | L829-1J1T-43 | L829-1J1T-43:L829-1J1T-43 | Footprints:BEL_L829-1J1T-43 |  | In Stock | https://www.snapeda.com/parts/L829-1J1T-43/Bel+Magnetic+Solu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 | MagJack 1000BASE-T | 1X1 | 3w-OG/Y | Tab Up | Low Profile | RoHS | 2675997 |  |  |  |  |  | Bel Fuse | 13.22 mm | Bel Magnetic Solutions | L829-1J1T-43 | K | None |  | None | https://www.snapeda.com/api/url_track_click_mouser/?unipart_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 |  | Manufacturer Recommendations | https://www.snapeda.com/parts/L829-1J1T-43/Bel+Magnetic+Solu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
21 | 1 | J2 | USB4085-GF-A_REVB | USB4085-GF-A_REVB:USB4085-GF-A_REVB | Footprints:GCT_USB4085-GF-A_REVB |  | In Stock | https://www.snapeda.com/parts/USB4085-GF-A/Global+Connector+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 | USB-C (USB TYPE-C) USB 2.0 Receptacle Connector 24 (16+8 Dummy) Position Throug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 | 2924867 |  |  |  |  |  | Global Connector Technology | 3.16mm | Global Connector Technology | USB4085-GF-A | B | None |  | None |  | USB4085-GF-A | Manufacturer Recommendations | https://www.snapeda.com/parts/USB4085-GF-A/Global+Connector+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
22 | 1 | J3 | 24v Input | Connector:Screw_Terminal_01x02 | TerminalBlock:TerminalBlock_bornier-2_P5.08mm | ~ |  |  |  | 2315262
23 | 1 | J4 | Screw_Terminal_01x04 | Connector:Screw_Terminal_01x04 | TerminalBlock:TerminalBlock_bornier-4_P5.08mm | ~ |  |  |  | 4179100
24 | 2 | JP1, JP4 | LRCK | Jumper:SolderJumper_2_Open | Jumper:SolderJumper-2_P1.3mm_Open_TrianglePad1.0x1.5mm | ~
25 | 2 | JP2, JP9 | D | Jumper:SolderJumper_2_Open | Jumper:SolderJumper-2_P1.3mm_Open_TrianglePad1.0x1.5mm | ~
26 | 2 | JP3, JP6 | BCK | Jumper:SolderJumper_2_Open | Jumper:SolderJumper-2_P1.3mm_Open_TrianglePad1.0x1.5mm | ~
27 | 1 | JP5 | SDA | Jumper:SolderJumper_2_Open | Jumper:SolderJumper-2_P1.3mm_Open_TrianglePad1.0x1.5mm | ~
28 | 1 | JP7 | SCL | Jumper:SolderJumper_2_Open | Jumper:SolderJumper-2_P1.3mm_Open_TrianglePad1.0x1.5mm | ~
29 | 1 | JP8 | MCK | Jumper:SolderJumper_2_Open | Jumper:SolderJumper-2_P1.3mm_Open_TrianglePad1.0x1.5mm | ~
30 | 1 | L1 | SRN6045TA-3R3Y | pspice:INDUCTOR | Inductor_SMD:L_Bourns_SRN6045TA | https://www.bourns.com/docs/Product-Datasheets/SRN6045TA.pdf |  |  |  | 2616889 | Farnell | 2616889 | SRN6045TA-3R3Y | Bourns |  |  |  |  |  |  |  | 3.3ÂµH Semi-Shielded Wirewound Inductor 7.8A 21mOhm Nonstandard
31 | 4 | L2, L3, L4, L5 | 0.5u | Device:L | Inductor_SMD:L_Bourns_SRN6045TA | ~ |  |  |  | 3780754
32 | 1 | Module1 | ComputeModule4 | CM4IO:ComputeModule4-CM4 | Footprints:Raspberry-Pi-4-Compute-Module |  |  |  |  | 2427679 | Hirose | 2x DF40C-100DS-0.4V | 2off DF40C-100DS-0.4V | Hirose |  |  |  |  |  |  |  | 100 Position Connector Receptacle, Center Strip Contacts Surface Mount Gold
33 | 1 | Q1 | DMP3013SFV-7 | Transistor_FET:DMP3013SFV | Package_SON:Diodes_PowerDI3333-8 | https://www.diodes.com/assets/Datasheets/DMP3013SFV.pdf |  |  |  | 3405192 | Farnell | 3405192 | DMP3013SFV-7 | Diodes |  |  |  |  |  |  |  | DMP3013SFV-7 - Power MOSFET, P Channel, 30 V, 12 A, 0.008 ohm, PowerDI3333, Sur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

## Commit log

2023-11-14 - First checkin
2023-11-15 - USB sound wired
2023-11-15 WM8804 via i2c
2023-11-17 - work in progress
2023-11-18 - voor aanpassing design rules jclpcb
2023-11-18 - amp connected
2023-11-20 - cleanup ERC errors
2023-11-20 - update gitignore, add pcb
2023-11-20 - pcb saved
2023-11-25 - ERC checks
2023-11-27 - work in progress, changed rj45 connector
2023-11-29 - placing components
2023-11-30 - component selection/place
2023-11-30 - wiring
2023-12-02 - component placed
2023-12-04 - routed
2023-12-05 - add production gerber
2023-12-10 - BOM added (Farnell nrs)
2023-12-28 - first checkin of software
2023-12-29 - compiles, not working
2023-12-30 - small (non functional) changes
2024-01-03 - test pcb
2024-01-06 - before chaging USB-DAC solution
2024-01-06 - usb dac added
2024-01-18 - power routed, locked
